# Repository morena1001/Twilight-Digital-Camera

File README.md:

# Twilight-Digital-Camera
This digital camera uses the OV2640 camera sensor on the Seeed Studio XIAO ESP32 S3 Sense to take pictures, and DSP to apply a filter to achieve that iconic Twilight movie look.

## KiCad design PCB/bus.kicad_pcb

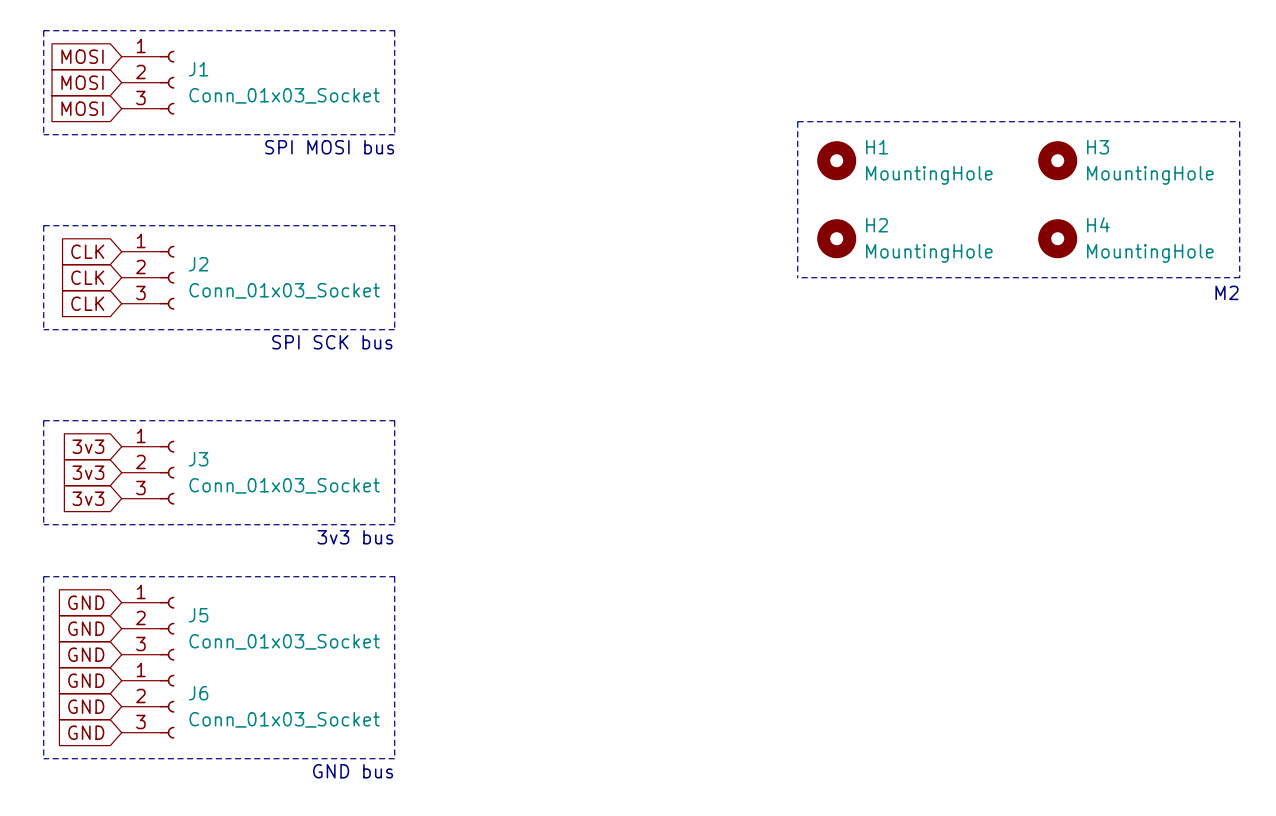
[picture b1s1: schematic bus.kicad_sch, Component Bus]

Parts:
H1, H2, H3, H4: MountingHole; MountingHole_2.2mm_M2
J1, J2, J3, J5, J6: Conn_01x03_Socket; PinHeader_1x03_P2.54mm_Vertical

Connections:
3v3: J3.1, J3.2, J3.3
CLK: J2.1, J2.2, J2.3
GND: J5.1, J5.2, J5.3, J6.1, J6.2, J6.3
MOSI: J1.1, J1.2, J1.3

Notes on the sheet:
SPI SCK bus
GND bus
SPI MOSI bus
3v3 bus

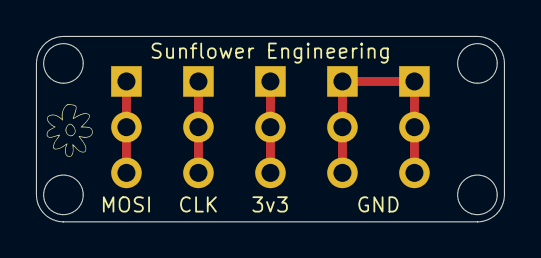
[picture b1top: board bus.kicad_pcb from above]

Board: 2 copper layers, 26.0 x 10.3 mm, 9 parts (0 on the bottom side), 4 nets.
